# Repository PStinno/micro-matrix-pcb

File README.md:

# µMatrix PCB
Small pcb design (< 1 inch square) with an onboard 5x7 LED matrix, controllable over I2C.

The LED matrix display used is the LTP-305/G from Lite-On Inc. The IS31FL3730 LED matrix driver IC, from ISSI Inc., is used to drive the matrix and provide control over I2C. The I2C address can be selected with solder jumpers on the back of the board from four possible options. It is compatible with power and logic at both 3.3 and 5V.

Also included in this repository is a simple software example for driving the display with an Arduino Uno or similar microcontroller development board. The basic implementation allows for displaying of text on the matrix, either flashed one character at a time or scrolled continuously across the display. Currently the font only supports the capital letters from A-Z and spaces.

[![CC BY-SA 4.0][cc-by-sa-image]][cc-by-sa]

[cc-by-sa]: http://creativecommons.org/licenses/by-sa/4.0/
[cc-by-sa-image]: https://licensebuttons.net/l/by-sa/4.0/88x31.png
[cc-by-sa-shield]: https://img.shields.io/badge/License-CC%20BY--SA%204.0-lightgrey.svg

This work is licensed under a [Creative Commons Attribution-ShareAlike 4.0 International License][cc-by-sa].

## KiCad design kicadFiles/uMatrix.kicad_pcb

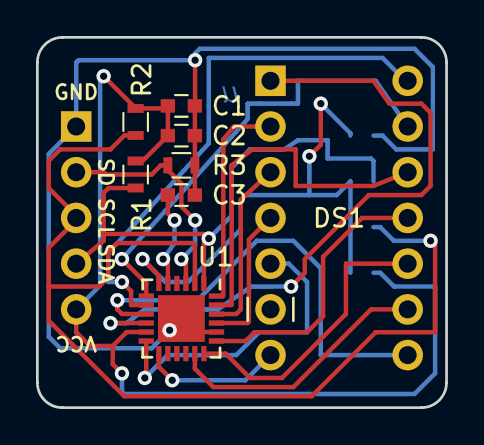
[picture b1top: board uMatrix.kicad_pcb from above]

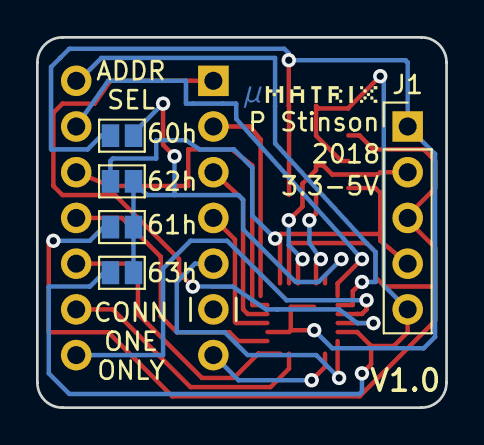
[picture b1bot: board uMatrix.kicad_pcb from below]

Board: 2 copper layers, 22.7 x 20.6 mm, 13 parts (5 on the bottom side), 20 nets.

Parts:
60h, 61h, 62h, 63h: Jumper_NO_Small; GS2
C1: 1uF; C_0603
C2, C3: 0.1uF; C_0603
DS1: LTP-305
J1: Conn_01x05; Pin_Header_Straight_1x05_Pitch2.54mm
R1, R2: 10K; R_0603
R3: 100K; R_0603
U1: IS31FL3730; QFN-24-1EP_4x4mm_Pitch0.5mm

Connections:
/AD: 60h.1, 61h.1, 62h.1, 63h.1, U1.6
/C1: DS1.5, U1.12
/C2: DS1.1, U1.10
/C3: DS1.8, U1.9
/C4: DS1.14, U1.8
/C5: DS1.13, U1.7
/DP: DS1.7, U1.13
/R1: DS1.2, U1.24
/R2: DS1.12, U1.23
/R3: DS1.3, U1.22
/R4: DS1.4, U1.21
/R5: DS1.11, U1.19
/R6: DS1.10, U1.18
/R7: DS1.9, U1.17
/SCL: 61h.2, J1.3, R2.2, U1.2
/SDA: 62h.2, J1.4, R1.2, U1.1
GND: 60h.2, C1.2, C2.2, C3.2, J1.1, R3.2, U1.20, U1.25
unnamed: C3.1, U1.5
unnamed: J1.2, R3.1, U1.3
VCC: 63h.2, C1.1, C2.1, J1.5, R1.1, R2.1, U1.11

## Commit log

2020-03-18 Create images directory
2020-03-18 Upload project images
2020-03-18 Fix image directory name
2020-03-18 Add Kicad design files and Arduino example code
2022-04-14 Added license file
